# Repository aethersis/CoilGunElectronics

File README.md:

# CoilGunElectronics
A collection of parts needed to build multistage coil guns. I try to design everything so that it can take up to 600V. Coating solder joints with special insulating varnish is still recommended. The coil gun stages are designed for 400V 470uF or 1000uF capacitors and the traces should be additionally plated with thick layer of solder or a wire should be soldered alongside those traces.

See http://digitalghosts.blog for more details.

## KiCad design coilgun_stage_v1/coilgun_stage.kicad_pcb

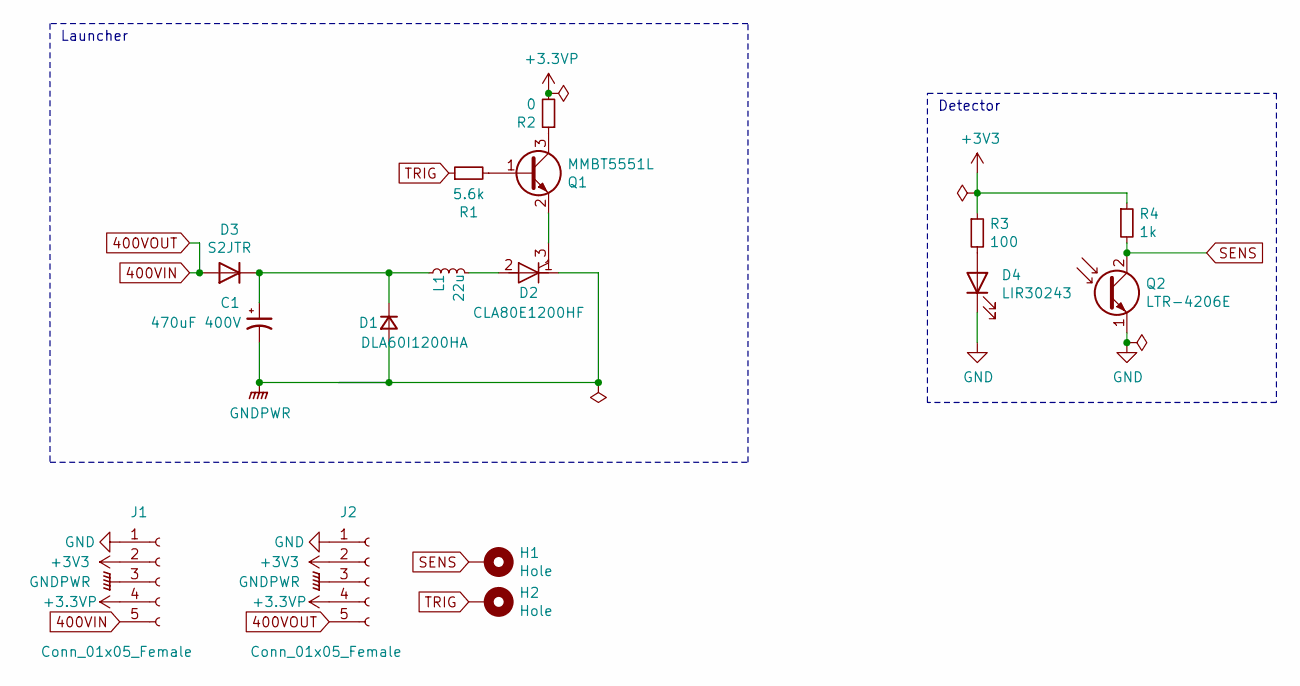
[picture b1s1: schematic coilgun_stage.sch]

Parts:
C1: 470uF 400V; CP_Radial_D35.0mm_P10.00mm_SnapIn
D1: DLA60I1200HA; TO-247-2_Vertical
D2: CLA80E1200HF; TO-247-3_Vertical
D3: S2JTR; D_SMB
D4: LIR30243; JST_PH_B2B-PH-K_1x02_P2.00mm_Vertical
H1, H2: Hole; PinHeader_1x01_P2.00mm_Vertical
J1, J2: Conn_01x05_Female; PinHeader_1x07_P2.54mm_Horizontal_3_6_missing
L1: 22u; L_Axial_L17.5mm_D12.0mm_P20.32mm_Horizontal_Vishay_IM-10-46
Q1: MMBT5551L; SOT-23
Q2: LTR-4206E; JST_PH_B2B-PH-K_1x02_P2.00mm_Vertical
R1: 5.6k; R_0603_1608Metric_Pad0.98x0.95mm_HandSolder
R2: 0; R_0603_1608Metric_Pad0.98x0.95mm_HandSolder
R3: 100; R_0603_1608Metric_Pad0.98x0.95mm_HandSolder
R4: 1k; R_0603_1608Metric_Pad0.98x0.95mm_HandSolder

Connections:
400VIN: D3.2 (A), J1.5, J2.5
+3.3VP: J1.4, J2.4, R2.2
+3V3: J1.2, J2.2, R3.1, R4.1
GND: D4.1 (K), J1.1, J2.1, Q2.1 (E)
GNDPWR: C1.2, D1.2 (A), D2.1 (K), J1.3, J2.3
unnamed: C1.1, D1.1 (K), D3.1 (K), L1.1
unnamed: D2.2 (A), L1.2
unnamed: D2.3 (G), Q1.2 (E)
unnamed: D4.2 (A), R3.2
unnamed: Q1.1 (B), R1.2
unnamed: Q1.3 (C), R2.1
SENS: H1.1, Q2.2 (C), R4.2
TRIG: H2.1, R1.1

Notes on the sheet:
Detector
Launcher

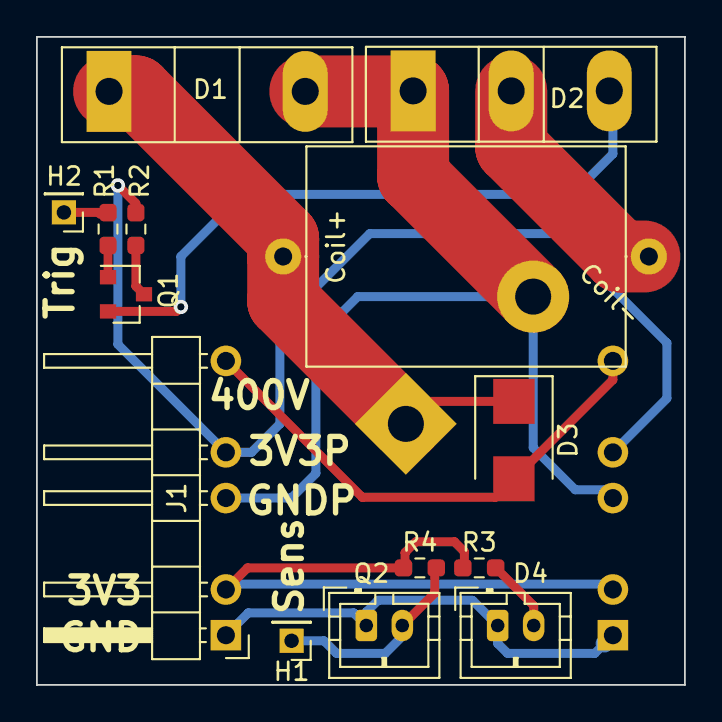
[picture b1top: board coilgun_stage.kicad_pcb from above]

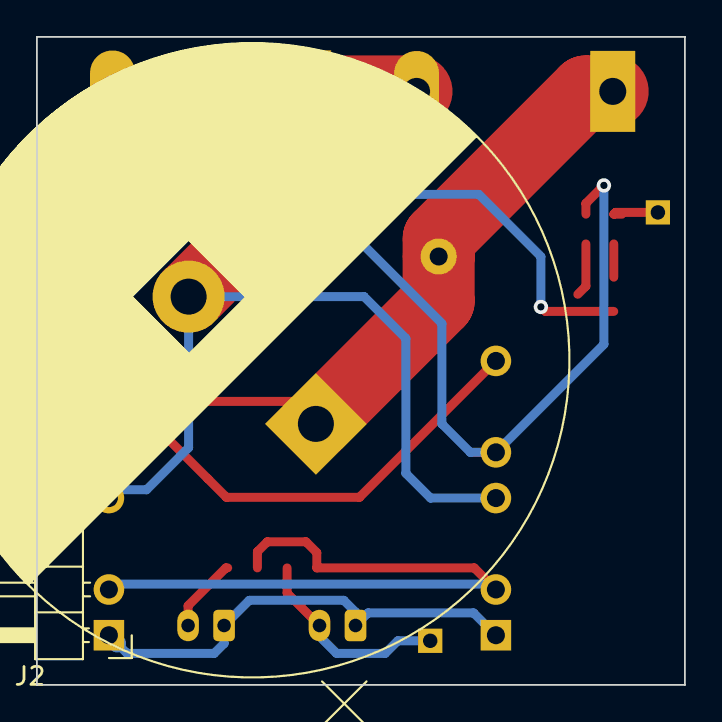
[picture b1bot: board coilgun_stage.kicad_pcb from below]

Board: 2 copper layers, 36.0 x 36.0 mm, 16 parts (2 on the bottom side), 13 nets.

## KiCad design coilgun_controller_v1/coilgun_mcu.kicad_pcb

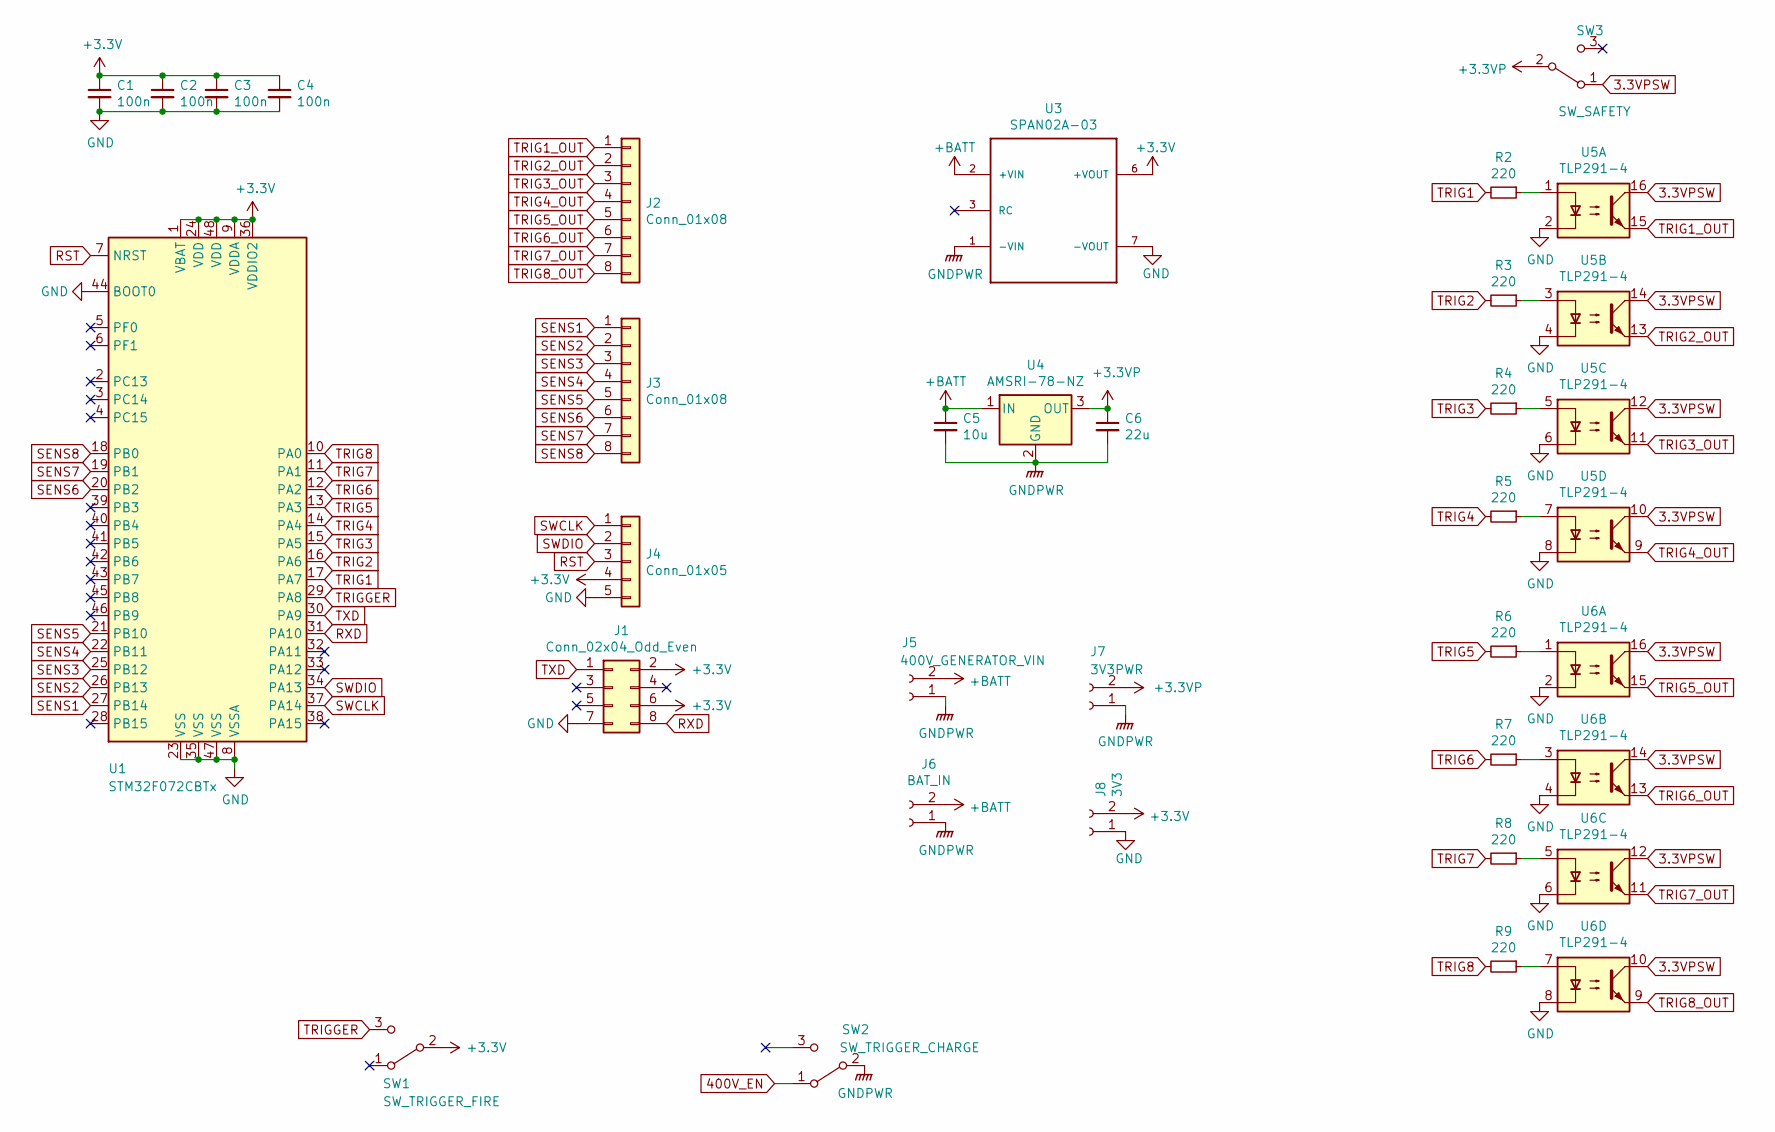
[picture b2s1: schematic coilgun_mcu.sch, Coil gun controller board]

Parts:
C1, C2, C3, C4: 100n; C_0603_1608Metric_Pad1.08x0.95mm_HandSolder
C5: 10u; C_0805_2012Metric
C6: 22u; C_0805_2012Metric
J1: Conn_02x04_Odd_Even; PinHeader_2x04_P2.54mm_Vertical
J2, J3: Conn_01x08; PinHeader_1x08_P2.54mm_Vertical
J4: Conn_01x05; PinHeader_1x05_P2.54mm_Vertical
J5: 400V_GENERATOR_VIN; PhoenixContact_MCV_1,5_2-G-5.08_1x02_P5.08mm_Vertical
J6: BAT_IN; PhoenixContact_MCV_1,5_2-G-5.08_1x02_P5.08mm_Vertical
J7: 3V3PWR; PinHeader_1x02_P2.54mm_Vertical
J8: 3V3; PinHeader_1x02_P2.54mm_Vertical
R2, R3, R4, R5, R6, R7, R8, R9: 220; R_0603_1608Metric_Pad0.98x0.95mm_HandSolder
SW1: SW_TRIGGER_FIRE; JST_PH_B3B-PH-K_1x03_P2.00mm_Vertical
SW2: SW_TRIGGER_CHARGE; JST_PH_B3B-PH-K_1x03_P2.00mm_Vertical
SW3: SW_SAFETY; JST_PH_B3B-PH-K_1x03_P2.00mm_Vertical
U1: STM32F072CBTx; LQFP-48_7x7mm_P0.5mm
U3: SPAN02A-03; SPAN02; PARTNO 1866-4766-ND
U4: AMSRI-78-NZ; TO-220-3_Vertical
U5, U6: TLP291-4; SOIC-16_4.55x10.3mm_P1.27mm

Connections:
3.3VPSW: SW3.1 (A), U5.10, U5.12, U5.14, U5.16, U6.10, U6.12, U6.14, U6.16
400V_EN: SW2.1 (A)
+3.3VP: C6.1, J7.2, SW3.2 (B), U4.3 (OUT)
+3V3: C1.1, C2.1, C3.1, C4.1, J1.2, J1.6, J4.4, J8.2, SW1.2 (B), U1.1 (VBAT), U1.9 (VDDA), U1.24 (VDD), U1.36 (VDDIO2), U1.48 (VDD), U3.6 (+VOUT)
+BATT: C5.1, J5.2, J6.2, U3.2 (+VIN), U4.1 (IN)
GND: C1.2, C2.2, C3.2, C4.2, J1.7, J4.5, J8.1, U1.8 (VSSA), U1.23 (VSS), U1.35 (VSS), U1.44 (BOOT0), U1.47 (VSS), U3.7 (-VOUT), U5.2, U5.4, U5.6, U5.8, U6.2, U6.4, U6.6, U6.8
GNDPWR: C5.2, C6.2, J5.1, J6.1, J7.1, SW2.2 (B), U3.1 (-VIN), U4.2 (GND)
unnamed: R2.1, U5.1
unnamed: R3.1, U5.3
unnamed: R4.1, U5.5
unnamed: R5.1, U5.7
unnamed: R6.1, U6.1
unnamed: R7.1, U6.3
unnamed: R8.1, U6.5
unnamed: R9.1, U6.7
RST: J4.3, U1.7 (NRST)
RXD: J1.8, U1.31 (PA10)
SENS1: J3.1, U1.27 (PB14)
SENS2: J3.2, U1.26 (PB13)
SENS3: J3.3, U1.25 (PB12)
SENS4: J3.4, U1.22 (PB11)
SENS5: J3.5, U1.21 (PB10)
SENS6: J3.6, U1.20 (PB2)
SENS7: J3.7, U1.19 (PB1)
SENS8: J3.8, U1.18 (PB0)
SWCLK: J4.1, U1.37 (PA14)
SWDIO: J4.2, U1.34 (PA13)
TRIG1: R2.2, U1.17 (PA7)
TRIG1_OUT: J2.1, U5.15
TRIG2: R3.2, U1.16 (PA6)
TRIG2_OUT: J2.2, U5.13
TRIG3: R4.2, U1.15 (PA5)
TRIG3_OUT: J2.3, U5.11
TRIG4: R5.2, U1.14 (PA4)
TRIG4_OUT: J2.4, U5.9
TRIG5: R6.2, U1.13 (PA3)
TRIG5_OUT: J2.5, U6.15
TRIG6: R7.2, U1.12 (PA2)
TRIG6_OUT: J2.6, U6.13
TRIG7: R8.2, U1.11 (PA1)
TRIG7_OUT: J2.7, U6.11
TRIG8: R9.2, U1.10 (PA0)
TRIG8_OUT: J2.8, U6.9
TRIGGER: SW1.3 (C), U1.29 (PA8)
TXD: J1.1, U1.30 (PA9)

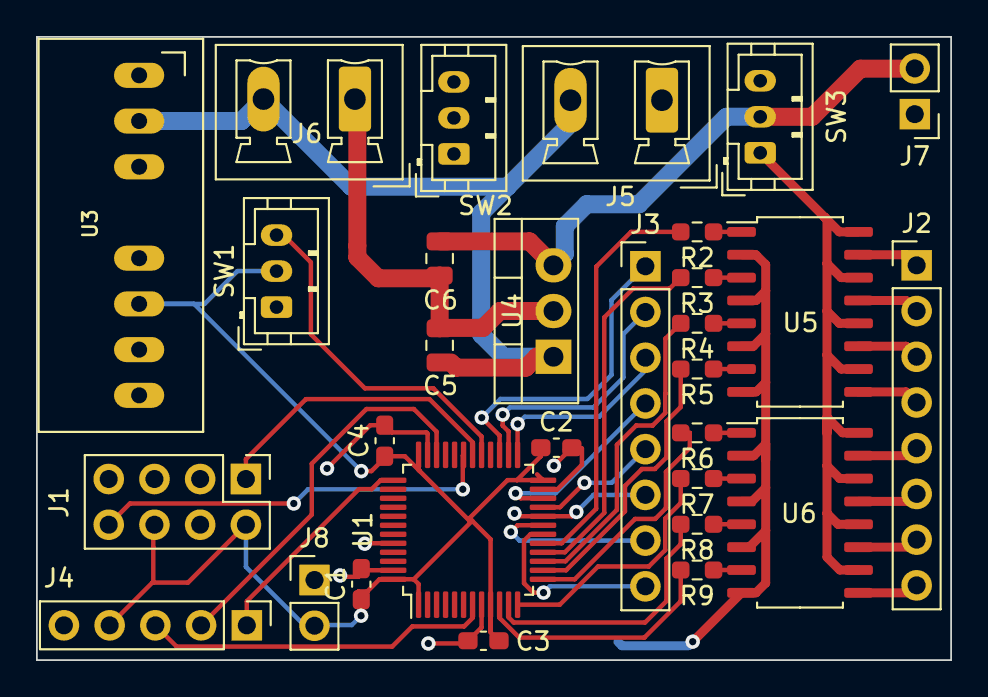
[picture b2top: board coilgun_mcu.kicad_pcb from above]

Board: 2 copper layers, 50.8 x 34.6 mm, 30 parts (0 on the bottom side), 44 nets.

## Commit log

2021-06-03 Add the electronics for the first revision
2021-06-05 Increase track clearance, cosmetic fixes
2021-06-25 Get rid of the useless optocoupler
2021-06-30 Fix swapped labels
